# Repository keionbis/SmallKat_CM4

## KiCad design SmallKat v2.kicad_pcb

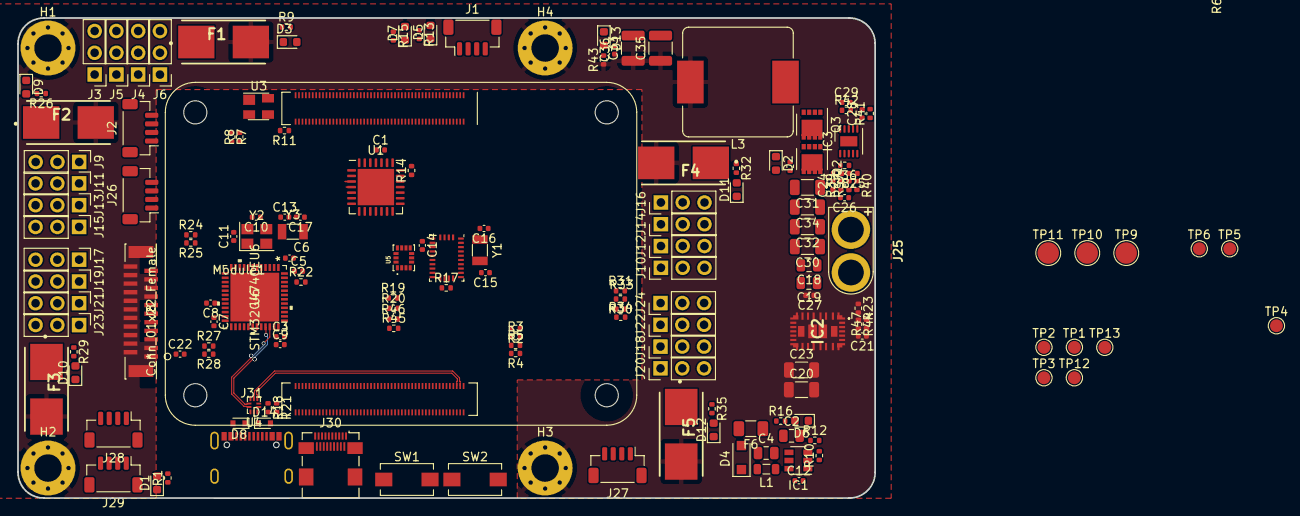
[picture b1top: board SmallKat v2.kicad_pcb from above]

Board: 4 copper layers, 100.0 x 56.0 mm, 167 parts (0 on the bottom side), 122 nets.

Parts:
C1, C12, C14, C22: 0.1uF; C_0402_1005Metric
C2: 2.2uF; C_0805_2012Metric
C3, C5, C6, C7, C8, C9, C10, C11, C13, C17, C21: C; C_0402_1005Metric
C4: 10uF; C_0805_2012Metric
C15, C16: 10pF; C_0402_1005Metric
C18, C19: C; C_0805_2012Metric
C20, C23: C; C_1206_3216Metric
C24: 1000pF; C_0402_1005Metric
C25: 100pF; C_0402_1005Metric
C26: 10nF; C_0402_1005Metric
C27, C36: 1uF; C_0402_1005Metric
C28: 4.7uF; C_0402_1005Metric
C29: 470nF; C_0402_1005Metric
C30, C32: 10uF; C_1206_3216Metric
C31, C34: 47uF; C_1206_3216Metric
C33, C35: 100uF; C_1210_3225Metric
D1, D2, D3, D5, D6, D7, D9, D10, D11, D12, D13: LED; LED_0603_1608Metric
D4: DIODE; D_SOD-123F
D8, D14: D_TVS; D_SOD-523
F1, F2, F3, F4, F5: Fuse; 0154.250DR
F6: Fuse; Fuse_1206_3216Metric
H1, H2, H3, H4: MountingHole_Pad; MountingHole_3.2mm_M3_Pad_Via
IC1: LMR14010A; SOT-23-6
IC2: TLVM13630
IC3: TPS40192DRCT-TPS40192DRCT; VSON-10-1EP_3x3mm_P0.5mm_EP1.2x2mm
J1, J2, J26, J27, J28, J29: Qwiic connector; JST_SH_BM04B-SRSS-TB_1x04-1MP_P1.00mm_Vertical
J3, J4, J5, J6, J9, J10, J11, J12, J13, J14, J15, J16, J17, J18, J19, J20, J21, J22, J23, J24: Conn_01x03_Male; PinHeader_1x03_P2.54mm_Vertical
J8: Conn_01x22_Female; XF2J-2224-12A
J25: Conn_01x02_Female; XT-30_female
J30: HDMI_A_1.4; HDMI_Micro-D_Molex_46765-0x01
J31: USB_C_Receptacle; C167321
L1: 10uH; L_0805_2012Metric
L3: 1uH; L_Bourns_SRP1245A
Module1: ComputeModule4-CM4; Raspberry-Pi-4-Compute-Module
Q2, Q3: BUK9M17-30EX / BUK7M10-40E; VSON-8_3.3x3.3mm_P0.65mm_NexFET
R1, R16: 330R; R_0402_1005Metric
R2, R4, R7, R10, R14, R17, R19, R20, R24, R27, R30, R33, R45, R46: 10K; R_0402_1005Metric
R3: 2.4K; R_0402_1005Metric
R5, R8, R25, R28, R31, R34: 8.2K; R_0402_1005Metric
R6: 120K; R_0402_1005Metric
R9, R26, R29, R32, R35: 20K; R_0402_1005Metric
R11, R13, R15, R18, R21, R22, R23, R44, R47: R; R_0402_1005Metric
R12: 33.2; R_0402_1005Metric
R36: 2.18k; R_0402_1005Metric
R37: 20k; R_0402_1005Metric
R38: 2.61k; R_0402_1005Metric
R39: 4.22k; R_0402_1005Metric
R40: 12k; R_0402_1005Metric
R41, R42: 100k; R_0402_1005Metric
R43: 1K; R_0402_1005Metric
SW1, SW2: SW_SPST; SW_SPST_EVQPE1
TP1: Check for life; TestPoint_Pad_D1.5mm
TP2, TP12: SDA; TestPoint_Pad_D1.5mm
TP3, TP13: SCL; TestPoint_Pad_D1.5mm
TP4: 3.3v; TestPoint_Pad_D1.5mm
TP5, TP6: TestPoint; TestPoint_Pad_D1.5mm
TP9: Batt+; TestPoint_Pad_D2.5mm
TP10: GND; TestPoint_Pad_D2.5mm
TP11: 6V; TestPoint_Pad_D2.5mm
U1: PCA9685BS; QFN-28-1EP_6x6mm_P0.65mm_EP4.25x4.25mm
U2: BNO055; LGA-28_5.2x3.8mm_P0.5mm
U3: 74LVC1G07; SOT-143
U4: FSUSB42MX; UQFN-10_1.4x1.8mm_P0.4mm
U5: ISM330DLCTR; PQFN50P250X300X86-14N
U6: STM32G474CEU6
Y1: 32.768kHz; Crystal_SMD_3215-2Pin_3.2x1.5mm
Y2: Crystal_GND24_Small; Crystal_SMD_Abracon_ABM8G-4Pin_3.2x2.5mm
Y3: Crystal_Small; Crystal_SMD_3215-2Pin_3.2x1.5mm

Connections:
+1V8: Module1.88 (+1.8v_(Output)), Module1.90 (+1.8v_(Output))
+3V3: C1.1, C3.1, C5.1, C6.1, C7.1, C8.1, C9.1, D5.2 (A), D7.2 (A), F6.1, J1.2, J2.2, J8.22, J26.2, J27.2, J28.2, J29.2, Module1.78 (GPIO_VREF(1.8v/3.3v_Input)), Module1.84 (+3.3v_(Output)), Module1.86 (+3.3v_(Output)), R12.1, R16.1, R19.2, R20.2, R45.2, R46.2, TP4.1, U1.25 (VDD), U2.3 (VDD), U2.4 (~nBOOT_LOAD_PIN), U2.28 (VDDIO), U4.1 (VCC), U5.5 (VDDIO), U5.8 (VDD), U5.12 (CS), U6.1 (VBAT), U6.20 (VREF+), U6.21 (VDDA), U6.23 (VDD), U6.35 (VDD), U6.48 (VDD)
+5V: C20.1, C23.1, IC2.7 (VOUT_1), IC2.8 (VOUT_2), IC2.9 (VOUT_3), IC2.10 (VOUT_4), IC2.12 (VOUT_5), IC2.13 (VOUT_6), IC2.14 (VOUT_7), IC2.15 (VOUT_8), IC2.22 (VLDOIN), IC2.30 (VOUT_9), IC2.33 (VOUT_10), IC2.34 (VOUT_11), IC2.35 (VOUT_12), IC2.36 (VOUT_13), J30.18 (+5V), Module1.77 (+5v_(Input)), Module1.79 (+5v_(Input)), Module1.81 (+5v_(Input)), Module1.83 (+5v_(Input)), Module1.85 (+5v_(Input)), Module1.87 (+5v_(Input)), R44.1
+6V: C24.1, C33.1, C35.1, C36.1, F1.2, F2.2, F3.2, F4.2, F5.2, H1.1, H2.1, H3.1, H4.1, L3.2, R4.1, R37.1, R43.1, TP11.1
+BATT: C2.1, C18.1, C19.1, C27.1, C30.1, C31.1, C32.1, C34.1, IC1.4 (EN), IC1.5 (VIN), IC2.2 (EN), IC2.3 (VIN_1), IC2.4 (VIN_2), IC2.18 (VIN_3), IC2.19 (VIN_4), IC3.4 (VDD), J25.2, Q2.5 (D), R2.1, R6.1, TP9.1
/BOOT0: Module1.24 (GPIO26), R22.1, U6.46 (PB8-BOOT0)
/CAM1_C_N: J8.8, Module1.127 (CAM1_C_N)
/CAM1_C_P: J8.9, Module1.129 (CAM1_C_P)
/CAM1_D0_N: J8.2, Module1.115 (CAM1_D0_N)
/CAM1_D0_P: J8.3, Module1.117 (CAM1_D0_P)
/CAM1_D1_N: J8.5, Module1.121 (CAM1_D1_N)
/CAM1_D1_P: J8.6, Module1.123 (CAM1_D1_P)
/CAM1_D2_N: J8.11, Module1.133 (CAM1_D2_N)
/CAM1_D2_P: J8.12, Module1.135 (CAM1_D2_P)
/CAM1_D3_N: J8.14, Module1.139 (CAM1_D3_N)
/CAM1_D3_P: J8.15, Module1.141 (CAM1_D3_P)
/CAM_GPIO: J8.17, Module1.97 (Camera_GPIO)
/HDMI0_CEC: J30.13 (CEC), Module1.151 (HDMI0_CEC)
/HDMI0_CK_N: J30.12 (CK-), Module1.190 (HDMI0_CLK_N)
/HDMI0_CK_P: J30.10 (CK+), Module1.188 (HDMI0_CLK_P)
/HDMI0_D0_N: J30.9 (D0-), Module1.184 (HDMI0_TX0_N)
/HDMI0_D0_P: J30.7 (D0+), Module1.182 (HDMI0_TX0_P)
/HDMI0_D1_N: J30.6 (D1-), Module1.178 (HDMI0_TX1_N)
/HDMI0_D1_P: J30.4 (D1+), Module1.176 (HDMI0_TX1_P)
/HDMI0_D2_N: J30.3 (D2-), Module1.172 (HDMI0_TX2_N)
/HDMI0_D2_P: J30.1 (D2+), Module1.170 (HDMI0_TX2_P)
/HDMI0_HOTPLUG: J30.19 (HPD/HEAC-), Module1.153 (HDMI0_HOTPLUG)
/HDMI0_SCL: J30.15 (SCL), Module1.200 (HDMI0_SCL)
/HDMI0_SDA: J30.16 (SDA), Module1.199 (HDMI0_SDA)
/MainBoard/AD_6V: F1.1, J3.2, J4.2, J5.2, J6.2, R7.1, R9.1
/MainBoard/AD_SERVO_1: J3.1, U6.38 (PA15)
/MainBoard/AD_SERVO_2: J5.1, U6.19 (PB2), U6.22 (PB10)
/MainBoard/AD_SERVO_3: J4.1, U6.24 (PB11)
/MainBoard/AD_SERVO_4: J6.1, U6.31 (PA9)
/MainBoard/BATT_VOLTAGE: R2.2, R3.1, U6.25 (PB12)
/MainBoard/BNO055/INT: U2.14 (INT), U5.4 (INT1)
/MainBoard/EN_SERVO_DRIVER: R14.1, U1.20 (~OE), U6.41 (PB3)
/MainBoard/ESP32Module/NRST: C22.1, SW2.2 (B), U6.7 (PG10-NRST)
/MainBoard/ESP32Module/PB6: R1.1, TP1.1, U6.44 (PB6)
/MainBoard/MEASURED_6V: R4.2, R5.1, U6.18 (PB1)
/MainBoard/RT: IC2.1 (RT_1), IC2.31 (RT_2), IC2.32 (RT_3), R23.2
/MainBoard/SCL: J2.4, J28.4, J29.4, R20.1, TP3.1, U2.19 (COM1), U5.13 (SCL), U6.30 (PA8)
/MainBoard/SCL_1: J1.4, J26.4, J27.4, R45.1, TP13.1, U1.23 (SCL), U6.45 (PB7)
/MainBoard/SDA: J2.3, J28.3, J29.3, R19.1, TP2.1, U2.20 (COM0), U5.14 (SDA), U6.40 (PC11)
/MainBoard/SDA_1: J1.3, J26.3, J27.3, R46.1, TP12.1, U1.24 (SDA), U6.29 (PC6)
/MainBoard/SERVO0: J9.1, U1.3 (LED0)
/MainBoard/SERVO1: J11.1, U1.4 (LED1)
/MainBoard/SERVO2: J13.1, U1.5 (LED2)
/MainBoard/SERVO3: J15.1, U1.6 (LED3)
/MainBoard/SERVO4: J17.1, U1.7 (LED4)
/MainBoard/SERVO5: J19.1, U1.8 (LED5)
/MainBoard/SERVO6: J21.1, U1.9 (LED6)
/MainBoard/SERVO7: J23.1, U1.10 (LED7)
/MainBoard/SERVO8: J10.1, U1.12 (LED8)
/MainBoard/SERVO9: J12.1, U1.13 (LED9)
/MainBoard/SERVO10: J14.1, U1.14 (LED10)
/MainBoard/SERVO11: J16.1, U1.15 (LED11)
/MainBoard/SERVO12: J18.1, U1.16 (LED12)
/MainBoard/SERVO13: J20.1, U1.17 (LED13)
/MainBoard/SERVO14: J22.1, U1.18 (LED14)
/MainBoard/SERVO15: J24.1, U1.19 (LED15)
/MainBoard/Servos/6V1: F2.1, J9.2, J11.2, J13.2, J15.2, R24.1, R26.1
/MainBoard/Servos/6V2: F3.1, J17.2, J19.2, J21.2, J23.2, R27.1, R29.1
/MainBoard/Servos/6V3: F4.1, J10.2, J12.2, J14.2, J16.2, R30.1, R32.1
/MainBoard/Servos/6V4: F5.1, J18.2, J20.2, J22.2, J24.2, R33.1, R35.1
/SEL: Module1.101 (USB_OTG_ID), R18.1, R21.1, U4.2 (SEL)
/USB2_N: Module1.103 (USB2_N), U4.4 (D_N)
/USB2_P: Module1.105 (USB2_P), U4.3 (D_P)
/USB_N: U4.6 (HSD0_M), U6.33 (PA11)
/USB_P: U4.7 (HSD0_P), U6.34 (PA12)
GND: C1.2, C2.2, C3.2, C4.2, C5.2, C6.2, C7.2, C8.2, C9.2, C10.2, C11.2, C13.2, C14.1, C15.1, C16.1, C17.2, C18.2, C19.2, C20.2, C21.1, C22.2, C23.2, C27.2, C28.2, C30.2, C31.2, C32.2, C33.2, C34.2, C35.2, C36.2, D1.1 (K), D2.1 (K), D3.1 (K), D6.1 (K), D8.2 (A2), D9.1 (K), D10.1 (K), D11.1 (K), D12.1 (K), D13.1 (K), D14.2 (A2), IC1.2 (GND), IC2.5 (PGND_1), IC2.6 (PGND_2), IC2.16 (PGND_3), IC2.17 (PGND_4), IC2.24 (AGND_1), IC2.27 (AGND_2), IC2.28 (PGND_5), IC2.29 (PGND_6), IC3.11 (GND), J1.1, J2.1, J3.3, J4.3, J5.3, J6.3, J8.1, J8.4, J8.7, J8.10, J8.13, J8.16, J8.19, J9.3, J10.3, J11.3, J12.3, J13.3, J14.3, J15.3, J16.3, J17.3, J18.3, J19.3, J20.3, J21.3, J22.3, J23.3, J24.3, J25.1, J26.1, J27.1, J28.1, J29.1, J30.2 (D2S), J30.5 (D1S), J30.8 (D0S), J30.11 (CKS), J30.17 (GND), J31.A1 (GND), J31.S1 (SHIELD), Module1.1 (GND), Module1.2 (GND), Module1.7 (GND), Module1.8 (GND), Module1.13 (GND), Module1.14 (GND), Module1.22 (GND), Module1.23 (GND), Module1.32 (GND), Module1.33 (GND), Module1.42 (GND), Module1.43 (GND), Module1.52 (GND), Module1.53 (GND), Module1.59 (GND), Module1.60 (GND), Module1.65 (GND), Module1.66 (GND), Module1.71 (GND), Module1.74 (GND), Module1.98 (GND), Module1.107 (GND), Module1.108 (GND), Module1.113 (GND), Module1.114 (GND), Module1.119 (GND), Module1.120 (GND), Module1.125 (GND), Module1.126 (GND), Module1.131 (GND), Module1.132 (GND), Module1.137 (GND), Module1.138 (GND), Module1.144 (GND), Module1.150 (GND), Module1.155 (GND), Module1.156 (GND), Module1.161 (GND), Module1.162 (GND), Module1.167 (GND), Module1.168 (GND), Module1.173 (GND), Module1.174 (GND), Module1.179 (GND), Module1.180 (GND), Module1.185 (GND), Module1.186 (GND), Module1.191 (GND), Module1.192 (GND), Module1.197 (GND), Module1.198 (GND), Q3.1 (S), Q3.2 (S), Q3.3 (S), R3.2, R5.2, R8.2, R10.1, R11.2, R14.2, R17.2, R18.2, R22.2, R23.1, R25.2, R28.2, R31.2, R34.2, R36.2, R40.2, R47.2, SW1.2 (B), SW2.1 (A), TP10.1, U1.1 (A3), U1.2 (A4), U1.11 (VSS), U1.21 (A5), U1.22 (EXTCLK), U1.26 (A0), U1.27 (A1), U1.28 (A2), U1.29 (VSS), U2.2 (GND), U2.5 (PS1), U2.6 (PS0), U2.15 (GNDIO), U2.16 (GNDIO), U2.18 (COM2), U2.25 (GNDIO), U3.3 (GND), U4.5 (GND), U4.10 (nOE), U5.1 (SDO/SAO), U5.2 (SDX), U5.3 (SCX), U5.6 (GND), U5.7 (GND), U6.49 (EPAD), Y2.2, Y2.4
MEASURED_FUSE1: R24.2, R25.1, U6.8 (PA0)
MEASURED_FUSE2: R27.2, R28.1, U6.9 (PA1)
MEASURED_FUSE3: R30.2, R31.1, U6.10 (PA2)
MEASURED_FUSE4: R33.2, R34.1, U6.11 (PA3)
MEASURED_FUSE5: R7.2, R8.1, U6.27 (PB14)
unnamed: C4.1, D4.1 (K), L1.2
unnamed: C10.1, U6.5 (PF0-OSC_IN), Y2.3
unnamed: C11.1, U6.6 (PF1-OSC_OUT), Y2.1
unnamed: C12.1, IC1.6 (SW), L1.1
unnamed: C12.2, IC1.1 (CB)
unnamed: C13.1, U6.3 (PC14-OSC32_IN), Y3.2
unnamed: C14.2, U2.9 (CAP)
unnamed: C15.2, U2.26 (XOUT32), Y1.1
unnamed: C16.2, U2.27 (XIN32), Y1.2
unnamed: C17.1, U6.4 (PC15-OSC32_OUT), Y3.1
unnamed: C21.2, IC2.23 (VCC)
unnamed: C24.2, R38.2
unnamed: C25.1, C26.1, IC3.3 (COMP), R40.1
unnamed: C25.2, IC3.2 (FB), R36.1, R37.2, R38.1, R39.2
unnamed: C26.2, R39.1
unnamed: C28.1, IC3.6 (BP5), R41.1
unnamed: C29.1, IC3.9 (SW), L3.1, Q2.1 (S), Q2.2 (S), Q2.3 (S), Q3.5 (D), R42.1
unnamed: C29.2, IC3.8 (BOOT), R42.2
unnamed: D1.2 (A), R1.2
unnamed: D2.2 (A), R6.2
unnamed: D3.2 (A), R9.2
unnamed: D4.2 (A), F6.2
unnamed: D5.1 (K), R13.2
unnamed: D6.2 (A), R16.2
unnamed: D7.1 (K), R15.2
unnamed: D8.1 (A1), J31.A7 (D-), J31.B7 (D-), U4.8 (HSD1_M)
unnamed: D9.2 (A), R26.2
unnamed: D10.2 (A), R29.2
unnamed: D11.2 (A), R32.2
unnamed: D12.2 (A), R35.2
unnamed: D13.2 (A), R43.2
unnamed: D14.1 (A1), J31.A6 (D+), J31.B6 (D+), U4.9 (HSD1_P)
unnamed: IC1.3 (FB), R10.2, R12.2
unnamed: IC2.25 (FB), R44.2, R47.1
unnamed: IC3.5 (PGD), R41.2
unnamed: IC3.7 (LDRV), Q3.4 (G)
unnamed: IC3.10 (HDRV), Q2.4 (G)
unnamed: J31.A4 (VBUS), R21.2
unnamed: Module1.21 (PI_nLED_Activity), R13.1
unnamed: Module1.93 (nRPIBOOT), SW1.1 (A)
unnamed: Module1.95 (nPI_LED_PWR), U3.2
unnamed: Module1.99 (Global_EN), R11.1
unnamed: R15.1, U3.4
unnamed: R17.1, U2.17 (COM3)
unnamed: TP5.1, U6.37 (PA14)
unnamed: TP6.1, U6.36 (PA13)

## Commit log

2021-10-18 added cm4

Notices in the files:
parts and their libraries:
Copyright 2021 Accelerated Designs. All rights reserved.
